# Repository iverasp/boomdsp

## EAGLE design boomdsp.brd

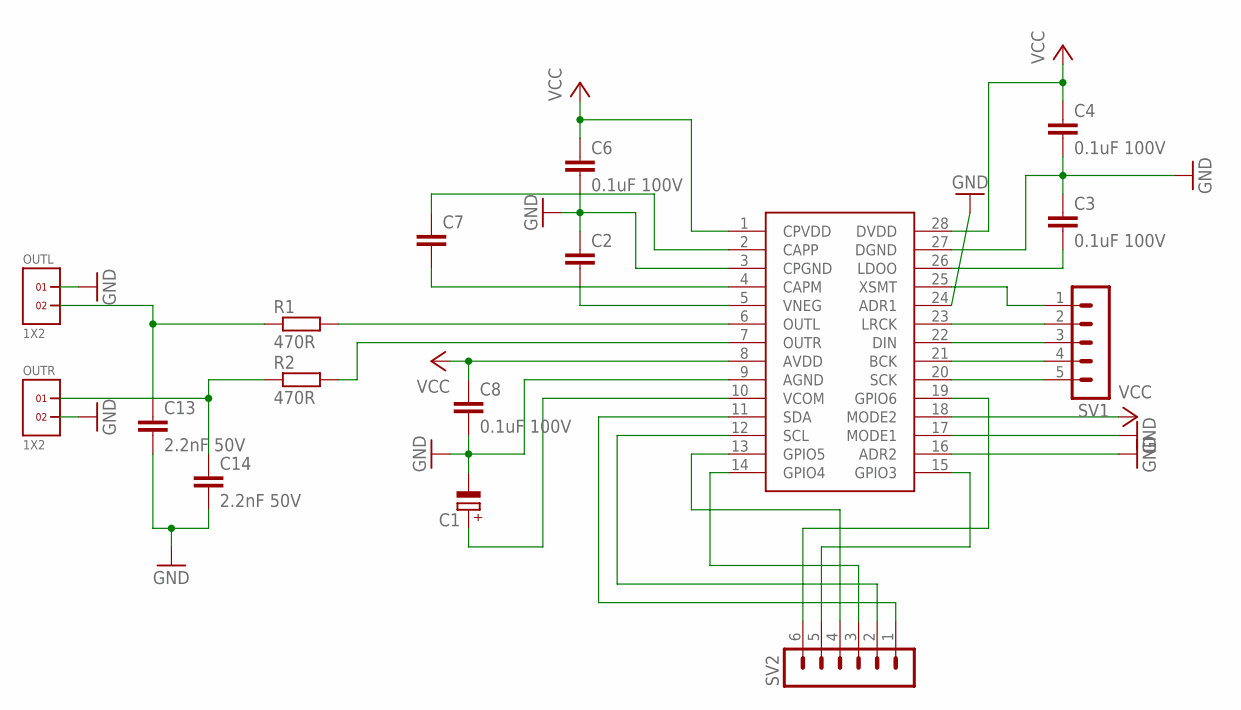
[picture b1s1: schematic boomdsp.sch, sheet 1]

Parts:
C1: CPOL-EUE3.5-8; E3,5-8
C2, C7: C-EUC0805; C0805
C3, C4, C6, C8: 0.1uF 100V; C0805
C13, C14: 2.2nF 50V; C102-043X133
OUTL: 1X2
OUTR: 1X2
R1, R2: 470R; R0805
SV1: MA05-1
SV2: MA06-1
U$1: PCM5142_I2C; TSSOP28

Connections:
GND: C1.-, C2.1, C3.1, C4.2, C6.2, C8.2, C13.2, C14.2, OUTL.1, OUTR.2, U$1.3 (CPGND), U$1.9 (AGND), U$1.16 (ADR2), U$1.17 (MODE1), U$1.24 (ADR1), U$1.27 (DGND); also elsewhere on the board
unnamed: R1.2, U$1.6 (OUTL)
unnamed: R2.2, U$1.7 (OUTR)
unnamed: C14.1, OUTR.1, R2.1
unnamed: C13.1, OUTL.2, R1.1
unnamed: C7.2, U$1.4 (CAPM)
unnamed: C3.2, U$1.26 (LDOO)
unnamed: SV2.5, U$1.15 (GPIO3)
unnamed: SV2.3, U$1.14 (GPIO4)
unnamed: C2.2, U$1.5 (VNEG)
unnamed: SV2.4, U$1.13 (GPIO5)
unnamed: SV2.6, U$1.19 (GPIO6)
unnamed: C7.1, U$1.2 (CAPP)
unnamed: SV1.2, U$1.23 (LRCK)
unnamed: SV1.3, U$1.22 (DIN)
unnamed: C1.+, U$1.10 (VCOM)
unnamed: SV1.4, U$1.21 (BCK)
unnamed: SV1.5, U$1.20 (SCK)
unnamed: SV2.1, U$1.11 (SDA)
unnamed: SV2.2, U$1.12 (SCL)
unnamed: SV1.1, U$1.25 (XSMT)
VCC: C4.1, C6.1, C8.1, U$1.1 (CPVDD), U$1.8 (AVDD), U$1.18 (MODE2), U$1.28 (DVDD); also elsewhere on the board

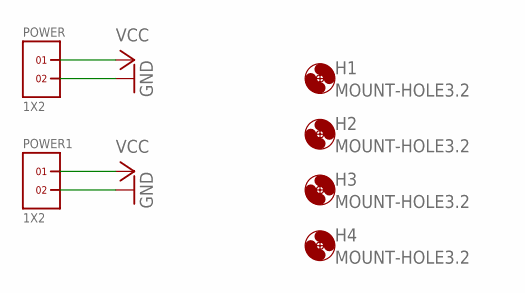
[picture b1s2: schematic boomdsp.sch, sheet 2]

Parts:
H1, H2, H3, H4: MOUNT-HOLE3.2; 3,2
POWER, POWER1: 1X2

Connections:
GND: POWER.2, POWER1.2; also elsewhere on the board
VCC: POWER.1, POWER1.1; also elsewhere on the board

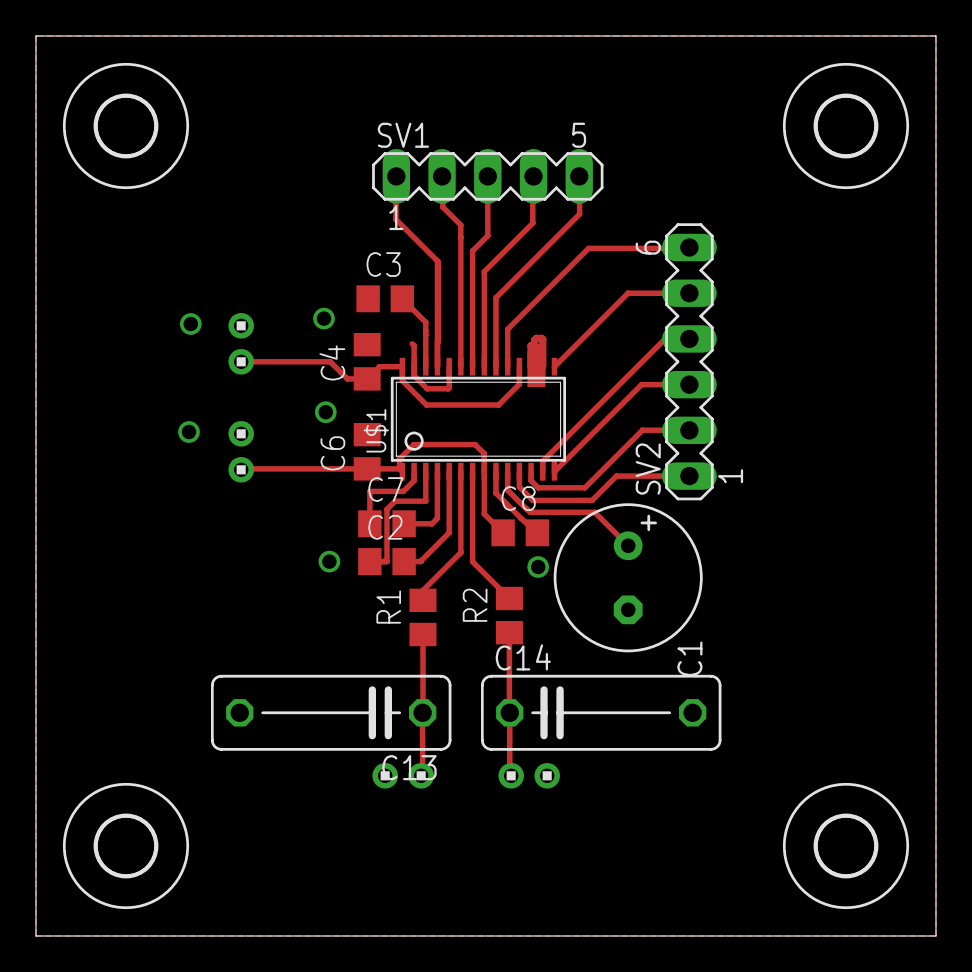
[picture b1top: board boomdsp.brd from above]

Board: 2 copper layers, 50.0 x 50.0 mm, 22 parts (0 on the bottom side), 22 nets.

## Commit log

2017-03-22 proto
2017-03-24 finished prototype
2017-03-25 damn vias
2017-03-25 via under chip. doesnt work for diy
2017-03-25 final prototype
